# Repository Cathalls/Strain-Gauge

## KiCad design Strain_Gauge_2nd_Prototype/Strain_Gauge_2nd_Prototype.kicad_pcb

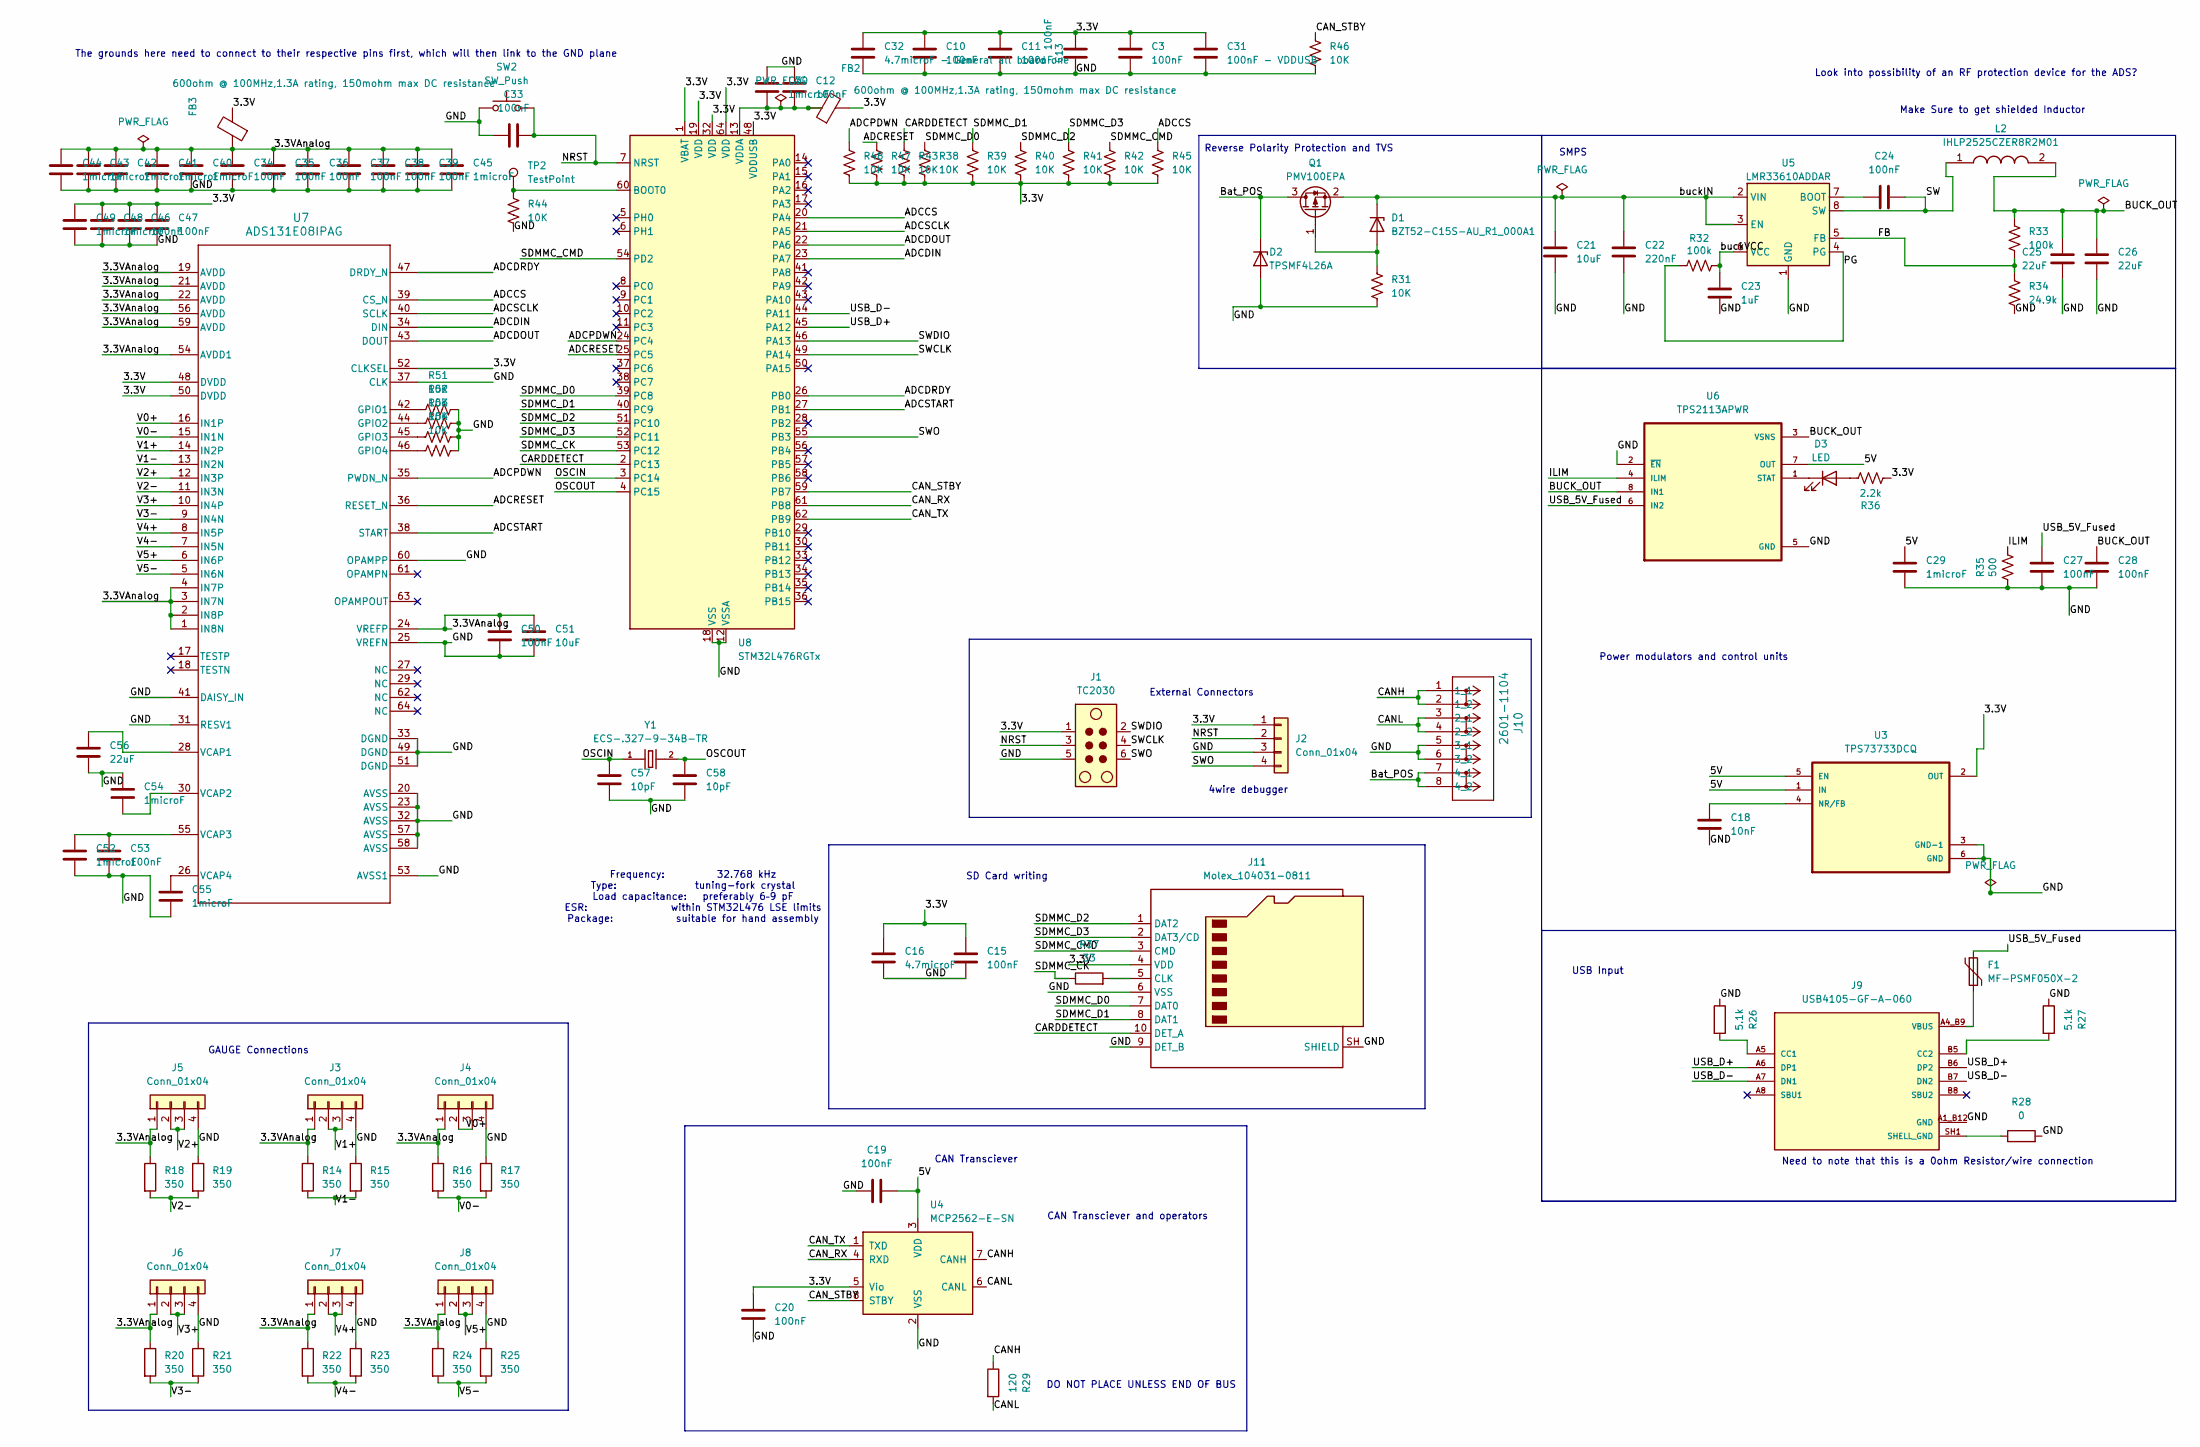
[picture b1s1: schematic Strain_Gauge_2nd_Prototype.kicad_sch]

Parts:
C3, C10, C11, C12, C13, C15, C19, C20, C24, C33, C34, C35, C36, C37, C38, C39, C46, C47, C50, C53: 100nF; C_0402_1005Metric_Pad0.74x0.62mm_HandSolder
C16: 4.7microF; C_0603_1608Metric_Pad1.08x0.95mm_HandSolder
C18: 10nF; C_0402_1005Metric_Pad0.74x0.62mm_HandSolder
C21, C51: 10uF; C_0805_2012Metric_Pad1.18x1.45mm_HandSolder
C22: 220nF; C_0402_1005Metric_Pad0.74x0.62mm_HandSolder
C23: 1uF; C_1206_3216Metric_Pad1.33x1.80mm_HandSolder
C25, C26, C56: 22uF; C_1206_3216Metric_Pad1.33x1.80mm_HandSolder
C27, C28: 100nF; C_0805_2012Metric_Pad1.18x1.45mm_HandSolder
C29: 1microF; C_0805_2012Metric_Pad1.18x1.45mm_HandSolder
C30, C40, C41, C42, C43, C44, C45, C48, C49, C52, C54, C55: 1microF; C_1206_3216Metric_Pad1.33x1.80mm_HandSolder
C31: 100nF - VDDUSB; C_0402_1005Metric_Pad0.74x0.62mm_HandSolder
C32: 4.7microF - General all board one; C_0603_1608Metric_Pad1.08x0.95mm_HandSolder
C57, C58: 10pF; C_0603_1608Metric_Pad1.08x0.95mm_HandSolder
D1: BZT52-C15S-AU_R1_000A1; D_SOD-323_HandSoldering
D2: TPSMF4L26A; D_SOD-123F
D3: LED; LED_0402_1005Metric
F1: MF-PSMF050X-2; Fuse_0805_2012Metric_Pad1.15x1.40mm_HandSolder
FB2, FB3: 600ohm @ 100MHz,1.3A rating, 150mohm max DC resis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; L_0603_1608Metric_Pad1.05x0.95mm_HandSolder
J1: TC2030; Tag-Connect_TC2030-IDC-NL_2x03_P1.27mm_Vertical
J2, J3, J4, J5, J6, J7, J8: Conn_01x04; SolderWire-0.25sqmm_1x04_P4.5mm_D0.65mm_OD2mm
J9: USB4105-GF-A-060; GCT_USB4105-GF-A-060; PARTREV B3
J10: 2601-1104; CONN4_2601-1104_WAG
J11: Molex_104031-0811; microSD_HC_Molex_104031-0811
L2: IHLP2525CZER8R2M01; INDPM6965X300N; Mouser Part Number 70-IHLP2525CZER8R2M1
Q1: PMV100EPA; SOT-23_Handsoldering
R14, R15, R16, R17, R18, R19, R20, R21, R22, R23, R24, R25: 350; R_Axial_DIN0207_L6.3mm_D2.5mm_P10.16mm_Horizontal
R26, R27: 5.1k; R_0402_1005Metric_Pad0.72x0.64mm_HandSolder
R28: 0; R_0402_1005Metric_Pad0.72x0.64mm_HandSolder
R29: 120; R_0402_1005Metric
R31, R38, R39, R40, R41, R42, R43, R44, R45, R46, R47, R48, R51, R52, R53, R54: 10K; R_0402_1005Metric_Pad0.72x0.64mm_HandSolder
R32: 100k; R_0805_2012Metric_Pad1.20x1.40mm_HandSolder
R33: 100k; R_0402_1005Metric
R34: 24.9k; R_0402_1005Metric_Pad0.72x0.64mm_HandSolder
R35: 500; R_0805_2012Metric_Pad1.20x1.40mm_HandSolder
R36: 2.2k; R_0402_1005Metric_Pad0.72x0.64mm_HandSolder
R37: 33; R_0402_1005Metric_Pad0.72x0.64mm_HandSolder
SW2: SW_Push; SW_PUSH_6mm
TP2: TestPoint; TestPoint_Pad_D1.5mm
U3: TPS73733DCQ; SOT127P706X180-6N
U4: MCP2562-E-SN; SOIC-8_3.9x4.9mm_P1.27mm
U5: LMR33610ADDAR; Texas_HSOP-8-1EP_3.9x4.9mm_P1.27mm_ThermalVias
U6: TPS2113APWR; SOP65P640X120-8N
U7: ADS131E08IPAG; PAG0064A_L
U8: STM32L476RGTx; LQFP-64_10x10mm_P0.5mm
Y1: ECS-.327-9-34B-TR; XTAL_ECS-.327-9-34B-TR

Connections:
/3.3V: C3.1, C10.2, C11.2, C13.2, C15.1, C16.1, C20.1, C31.1, C32.1, C46.2, C47.2, C48.1, C49.1, FB2.2, FB3.2, J1.1, J2.1, J11.4 (VDD), R36.1, R38.2, R39.2, R40.2, R41.2, R42.2, R43.2, R45.2, R47.2, R48.2, U3.2 (OUT), U4.5 (Vio), U7.48 (DVDD), U7.50 (DVDD), U7.52 (CLKSEL), U8.1 (VBAT), U8.19 (VDD), U8.32 (VDD), U8.48 (VDDUSB), U8.64 (VDD)
/3.3VAnalog: C34.2, C35.2, C36.2, C37.2, C38.2, C39.2, C40.1, C41.1, C42.1, C43.1, C44.1, C45.1, C50.2, C51.1, FB3.1, J3.1, J4.1, J5.1, J6.1, J7.1, J8.1, R14.1, R16.1, R18.1, R20.1, R22.1, R24.1, U7.1 (IN8N), U7.2 (IN8P), U7.3 (IN7N), U7.4 (IN7P), U7.19 (AVDD), U7.21 (AVDD), U7.22 (AVDD), U7.24 (VREFP), U7.54 (AVDD1), U7.56 (AVDD), U7.59 (AVDD)
/5V: C19.2, C29.1, U3.1 (IN), U3.5 (EN), U4.3 (VDD), U6.7 (OUT)
/ADCCS: R45.1, U7.39 (CS_N), U8.20 (PA4)
/ADCDIN: U7.34 (DIN), U8.23 (PA7)
/ADCDOUT: U7.43 (DOUT), U8.22 (PA6)
/ADCDRDY: U7.47 (DRDY_N), U8.26 (PB0)
/ADCPDWN: R48.1, U7.35 (PWDN_N), U8.24 (PC4)
/ADCRESET: R47.1, U7.36 (RESET_N), U8.25 (PC5)
/ADCSCLK: U7.40 (SCLK), U8.21 (PA5)
/ADCSTART: U7.38 (START), U8.27 (PB1)
/BUCK_OUT: C25.1, C26.1, C28.1, L2.2, R33.1, U6.3 (VSNS), U6.8 (IN1)
/Bat_POS: D2.1 (K), J10.7 (4_1), J10.8 (4_2), Q1.3 (D)
/CANH: J10.1 (1_1), J10.2 (1_2), R29.1, U4.7 (CANH)
/CANL: J10.3 (2_1), J10.4 (2_2), R29.2, U4.6 (CANL)
/CAN_RX: U4.4 (RXD), U8.61 (PB8)
/CAN_STBY: R46.1, U4.8 (STBY), U8.59 (PB7)
/CAN_TX: U4.1 (TXD), U8.62 (PB9)
/CARDDETECT: J11.10 (DET_A), R43.1, U8.2 (PC13)
/FB: R33.2, R34.1, U5.5 (FB)
/ILIM: R35.2, U6.4 (ILIM)
/NRST: C33.1, J1.3, J2.2, SW2.2, U8.7 (NRST)
/OSCIN: C57.1, U8.3 (PC14), Y1.1
/OSCOUT: C58.1, U8.4 (PC15), Y1.2
/PG: R32.1, U5.4 (PG)
/SDMMC_CK: R37.1, U8.53 (PC12)
/SDMMC_CMD: J11.3 (CMD), R42.1, U8.54 (PD2)
/SDMMC_D0: J11.7 (DAT0), R38.1, U8.39 (PC8)
/SDMMC_D1: J11.8 (DAT1), R39.1, U8.40 (PC9)
/SDMMC_D2: J11.1 (DAT2), R40.1, U8.51 (PC10)
/SDMMC_D3: J11.2 (DAT3/CD), R41.1, U8.52 (PC11)
/SW: C24.2, L2.1, U5.8 (SW)
/SWCLK: J1.4, U8.49 (PA14)
/SWDIO: J1.2, U8.46 (PA13)
/SWO: J1.6, J2.4, U8.55 (PB3)
/USB_5V_Fused: C27.1, F1.1, U6.6 (IN2)
/USB_D+: J9.A6 (DP1), J9.B6 (DP2), U8.45 (PA12)
/USB_D-: J9.A7 (DN1), J9.B7 (DN2), U8.44 (PA11)
/V0+: J4.2, J4.3, U7.16 (IN1P)
/V0-: R16.2, R17.2, U7.15 (IN1N)
/V1+: J3.2, J3.3, U7.14 (IN2P)
/V1-: R14.2, R15.2, U7.13 (IN2N)
/V2+: J5.2, J5.3, U7.12 (IN3P)
/V2-: R18.2, R19.2, U7.11 (IN3N)
/V3+: J6.2, J6.3, U7.10 (IN4P)
/V3-: R20.2, R21.2, U7.9 (IN4N)
/V4+: J7.2, J7.3, U7.8 (IN5P)
/V4-: R22.2, R23.2, U7.7 (IN5N)
/V5+: J8.2, J8.3, U7.6 (IN6P)
/V5-: R24.2, R25.2, U7.5 (IN6N)
/buckIN: C21.1, C22.1, D1.1 (K), Q1.2 (S), U5.2 (VIN), U5.3 (EN)
/buckVCC: C23.1, R32.2, U5.6 (VCC)
GND: C3.2, C10.1, C11.1, C12.2, C13.1, C15.2, C16.2, C18.2, C19.1, C20.2, C21.2, C22.2, C23.2, C25.2, C26.2, C27.2, C28.2, C29.2, C30.1, C31.2, C32.2, C33.2, C34.1, C35.1, C36.1, C37.1, C38.1, C39.1, C40.2, C41.2, C42.2, C43.2, C44.2, C45.2, C46.1, C47.1, C48.2, C49.2, C50.1, C51.2, C52.2, C53.1, C54.1, C55.2, C56.2, C57.2, C58.2, D2.2 (A), J1.5, J2.3, J3.4, J4.4, J5.4, J6.4, J7.4, J8.4, J9.A1_B12 (GND), J9.B1_A12 (GND), J10.5 (3_1), J10.6 (3_2), J11.6 (VSS), J11.9 (DET_B), J11.SH (SHIELD), R15.1, R17.1, R19.1, R21.1, R23.1, R25.1, R26.1, R27.1, R28.2, R31.2, R34.2, R35.1, R44.2, R46.2, R51.2, R52.2, R53.2, R54.2, SW2.1, U3.3 (GND-1), U3.6 (GND), U4.2 (VSS), U5.1 (GND), U5.9 (GND), U6.2 (~EN), U6.5 (GND), U7.20 (AVSS), U7.23 (AVSS), U7.25 (VREFN), U7.31 (RESV1), U7.32 (AVSS), U7.33 (DGND), U7.37 (CLK), U7.41 (DAISY_IN), U7.49 (DGND), U7.51 (DGND), U7.53 (AVSS1), U7.57 (AVSS), U7.58 (AVSS), U7.60 (OPAMPP), U8.12 (VSSA), U8.18 (VSS), U8.31 (VSS), U8.47 (VSS), U8.63 (VSS)
unnamed: D1.2 (A), Q1.1 (G), R31.1
unnamed: D3.2 (A), R36.2
unnamed: D3.1 (K), U6.1 (STAT)
unnamed: J9.A5 (CC1), R26.2
unnamed: J9.B5 (CC2), R27.2
unnamed: J9.SH1 (SHELL_GND), R28.1
unnamed: J11.5 (CLK), R37.2
unnamed: C18.1, U3.4 (NR/FB)
unnamed: C24.1, U5.7 (BOOT)
unnamed: R51.1, U7.42 (GPIO1)
unnamed: R52.1, U7.44 (GPIO2)
unnamed: R53.1, U7.45 (GPIO3)
unnamed: R54.1, U7.46 (GPIO4)
unnamed: C56.1, U7.28 (VCAP1)
unnamed: C54.2, U7.30 (VCAP2)
unnamed: C52.1, C53.2, U7.55 (VCAP3)
unnamed: C55.1, U7.26 (VCAP4)
unnamed: R44.1, TP2.1 (1_1), U8.60 (BOOT0)
unnamed: C12.1, C30.2, FB2.1, U8.13 (VDDA)
VBUS: F1.2, J9.A4_B9 (VBUS), J9.B4_A9 (VBUS)

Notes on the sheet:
SMPS
Need to note that this is a 0ohm Resistor/wire connection
Frequency: 32.768 kHz Type: tuning-fork crystal Load capacitance: preferably 6–9 pF ESR: within STM32L476 LSE limits Package: suitable for hand assembly
Power modulators and control units
Make Sure to get shielded Inductor
Reverse Polarity Protection and TVS
4wire debugger
USB Input
DO NOT PLACE UNLESS END OF BUS
Look into possibility of an RF protection device for the ADS?
SD Card writing
CAN Transciever and operators
GAUGE Connections
External Connectors
CAN Transciever
The grounds here need to connect to their respective pins first, which will then link to the GND plane

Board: 2 copper layers, 114 parts (0 on the bottom side), 73 nets, no tracks yet.

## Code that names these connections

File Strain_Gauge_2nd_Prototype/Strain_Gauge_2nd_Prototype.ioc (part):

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Mcu.Name=STM32L476R(C-E-G)Tx
Mcu.Package=LQFP64
Mcu.UserName=STM32L476RGTx
PA11.Mode=Device_Only
PA11.Signal=USB_OTG_FS_DM
PA12.Mode=Device_Only
PA12.Signal=USB_OTG_FS_DP
PA13\ (JTMS-SWDIO).Mode=Serial_Wire
PA13\ (JTMS-SWDIO).Signal=SYS_JTMS-SWDIO
PA14\ (JTCK-SWCLK).Mode=Serial_Wire
PA14\ (JTCK-SWCLK).Signal=SYS_JTCK-SWCLK
PA4.GPIOParameters=GPIO_Label
PA4.GPIO_Label=ADC_CS
PA4.Signal=GPIO_Output
PA5.Mode=Full_Duplex_Master
PA5.Signal=SPI1_SCK
PA6.Mode=Full_Duplex_Master
PA6.Signal=SPI1_MISO
PA7.Mode=Full_Duplex_Master
PA7.Signal=SPI1_MOSI
PB0.GPIOParameters=GPIO_Label,GPIO_ModeDefaultEXTI
PB0.GPIO_Label=ADC_DRDY
PB0.GPIO_ModeDefaultEXTI=GPIO_MODE_IT_FALLING
PB0.Signal=GPXTI0
PB1.GPIOParameters=GPIO_Label
PB1.GPIO_Label=ADC_START
PB1.Signal=GPIO_Output
PB3\ (JTDO-TRACESWO).Signal=SYS_JTDO-SWO
PB7.GPIOParameters=GPIO_Label
PB7.GPIO_Label=CAN_STBY
PB7.Signal=GPXTI7
PB8.Mode=CAN_Activate
PB8.Signal=CAN1_RX
PB9.Mode=CAN_Activate
PB9.Signal=CAN1_TX
PC10.Mode=SD_4_bits_Wide_bus
PC10.Signal=SDMMC1_D2
PC11.Mode=SD_4_bits_Wide_bus
PC11.Signal=SDMMC1_D3
PC12.Mode=SD_4_bits_Wide_bus
PC12.Signal=SDMMC1_CK
PC13.GPIOParameters=GPIO_Label
PC13.GPIO_Label=CARDDETECT
PC13.Signal=GPXTI13
PC14-OSC32_IN\ (PC14).Mode=LSE-External-Oscillator
PC14-OSC32_IN\ (PC14).Signal=RCC_OSC32_IN
PC15-OSC32_OUT\ (PC15).Mode=LSE-External-Oscillator
PC15-OSC32_OUT\ (PC15).Signal=RCC_OSC32_OUT
PC4.GPIOParameters=GPIO_Label
PC4.GPIO_Label=ADCPWDN
PC4.Signal=GPXTI4
PC5.GPIOParameters=GPIO_Label
PC5.GPIO_Label=ADCRESET
PC5.Signal=GPXTI5
PC8.Mode=SD_4_bits_Wide_bus
PC8.Signal=SDMMC1_D0
PC9.Mode=SD_4_bits_Wide_bus
PC9.Signal=SDMMC1_D1
PD2.Mode=SD_4_bits_Wide_bus
PD2.Signal=SDMMC1_CMD
RCC.HSE_VALUE=8192000
RCC.SYSCLKFreq_VALUE=80000000
RCC.SYSCLKSource=RCC_SYSCLKSOURCE_PLLCLK
board=custom
